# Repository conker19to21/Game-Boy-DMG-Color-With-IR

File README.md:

This Board is a modified version of <a href="https://github.com/MouseBiteLabs/Game-Boy-DMG-Color/tree/main/DMGC-CPU-01">Bucket Mouse's Original DMGC CPU board</a> which houses the majority of the electronics in the DMGC but adds the IR components and capability as well.

.png)
.png)

Shoutout to NatalieTheNerd for their amazing Reverse engineering work which was referrenced for this project and can be <a href="https://github.com/nataliethenerd/CGB_ReverseEngineer/tree/main">Found Here!</a>

Additional Major Shout Out goes to EdvinDraw!
A IR shield cutout was designed by EdvinDraw and can be <a href="https://www.thingiverse.com/thing:7093936">Found Here!</a> for use with NON clear DMG shells.

Additionally EdvinDraw had also made a Tutorial how to use and make the IR shield cutout which can be <a href="https://youtu.be/QVl8f0OApuU?si=GgzmjaVQX5JkgJGN">Found Here!</a>

Also note the IR was tested on some clear shells and worked fine without the cutout or IR shield but may still be needed for some.

Download and use the gerber.zip file at your preferred PCB manufacture and use these Board Characteristics for proper fitment.
## Board Characteristics
The gerber zipped folder contains all the gerber files for this board. 

-	Layers: 2
-	Thickness: 1.2 mm
-	Surface Finish: ENIG or HASL
-   **NOTE: When ordering PCBs, add this note to the order: "The file PTH-drl.gbr contains outlines for plated slots. Please add plated slots on the PCB according to this layer."**

*HASL will work, but will potentially be more difficult for soldering fine-pitch parts like the CPU and FFC connector.*

I do not take any credit for Bucket Mouse's Board Design only the modifications done and implementation for the IR components which were added to it.

Be sure to check out Bucket Mouse's Original Github Post on the DMGC project which can be <a href="https://github.com/MouseBiteLabs/Game-Boy-DMG-Color/tree/main">Found Here!</a> and has a Huge breakdown of common issues and solutions to most issues which may occur during the building process.

Version 2.0 of Bucket Mouse's original design introduced a test pad labelled "RST" that connects directly to the /RESET pin. If this pin is pulled to GND, when it's released then the system will reset back to the boot screen. If you wire this pad to a button that connects the pad to GND when pressed, you basically have added a reset button to your DMGC. 

There are also pads near the FFC connector that are added labelled "PUSH" and "ROCK DOWN". These connect to the rocker switch on the DMGC-IPS-01 board (version 2.0 and later). The PUSH pad becomes connected to GND when the rocker switch is pushed in and floats when not pressed (as long as you remove R10 on the DMGC-IPS-01 board). The ROCK_DOWN pad connects to GND when the rocker switch is rocked down, and floats when not pressed (as long as you remove C5 on the DMGC-IPS-01 board).

In a normal configuration, pushing in on the rocker switch will control the button LEDs, and rocking down will swap the Q5 color settings, but if you don't want to use one of these features, then adding a wire from the PUSH or ROCK DOWN pad to RST pad will turn the rocker switch into a reset button for the system for that specific action and replace its normal function.

**CAUTION: Remember to remove R10 or C5 on the IPS board if you plan to use this feature!!!**

## Bill of Materials

Here, I have provided links to components I used personally (or suitable replacements). This BOM is also included in Excel format in the root folder.

| Reference Designators                       | Qty | Value/Part Number | Package     | Description        | Comment                                                                 | Source                                                                                                                                                                                                                                                                                                                           |
| ------------------------------------------- | --- | ----------------- | ----------- | ------------------ | ----------------------------------------------------------------------- | -------------------------------------------------------------------------------------------------------------------------------------------------------------------------------------------------------------------------------------------------------------------------------------------------------------------------------- |
| +,-                                         | 2   |                   |             | Battery terminals  | Can be salvaged from DMG instead                                        | [https://retrogamerepairshop.com/collections/dmg-power/products/game-boy-dmg-original-high-quality-replacement-battery-contact-terminals?variant=37893135794348](https://retrogamerepairshop.com/collections/dmg-power/products/game-boy-dmg-original-high-quality-replacement-battery-contact-terminals?variant=37893135794348) |
| C1                                          | 1   | 18pF              | 0603        | Capacitor (MLCC)   | Should be X5R (or better); at least 1% tolerance; at least 16V          | [https://www.mouser.com/ProductDetail/YAGEO/CC0603FRNPO9BN180?qs=vTakOoo5QyL0KzYUzHPSUw%3D%3D](https://www.mouser.com/ProductDetail/YAGEO/CC0603FRNPO9BN180?qs=vTakOoo5QyL0KzYUzHPSUw%3D%3D)                                                                                                                                     |
| C2                                          | 1   | 27pF              | 0603        | Capacitor (MLCC)   | Should be X5R (or better); at least 1% tolerance; at least 16V          | [https://www.mouser.com/ProductDetail/603-C0603FRNPO9BN270](https://www.mouser.com/ProductDetail/603-C0603FRNPO9BN270)                                                                                                                                                                                                           |
| C4                                          | 1   | 22pF              | 0603        | Capacitor (MLCC)   |                                                                         | [https://www.mouser.com/ProductDetail/YAGEO/CC0603JRNPO9BN220?qs=vTakOoo5QyIVMYOUTI%2F4zA%3D%3D](https://www.mouser.com/ProductDetail/YAGEO/CC0603JRNPO9BN220?qs=vTakOoo5QyIVMYOUTI%2F4zA%3D%3D)                                                                                                                                 |
| C5, C6, C7                                  | 3   | 100pF             | 0603        | Capacitor (MLCC)   |                                                                         | [https://www.mouser.com/ProductDetail/YAGEO/CC0603JPNPO9BN101?qs=7s%252B3O6pAiyAo%2FUxNqKltRA%3D%3D](https://www.mouser.com/ProductDetail/YAGEO/CC0603JPNPO9BN101?qs=7s%252B3O6pAiyAo%2FUxNqKltRA%3D%3D)                                                                                                                         |
| C9, C10, C29, C33, C41, C45                 | 6   | 0.01uF            | 0603        | Capacitor (MLCC)   | Should be X5R (or better), at least 16V                                 | [https://www.mouser.com/ProductDetail/KEMET/C0603C103J5RACTU?qs=BimOss5pjlFJEfKhlb7g1g%3D%3D](https://www.mouser.com/ProductDetail/KEMET/C0603C103J5RACTU?qs=BimOss5pjlFJEfKhlb7g1g%3D%3D)                                                                                                                                       |
| C16, C17, C18, C19, C39, C40, C48, C49, C51 | 9   | 1uF               | 0603        | Capacitor (MLCC)   | Should be X5R (or better), at least 16V                                 | [https://www.mouser.com/ProductDetail/KEMET/C0603C105K4RACTU?qs=STjISULpmtZNMAZGR4X39Q%3D%3D](https://www.mouser.com/ProductDetail/KEMET/C0603C105K4RACTU?qs=STjISULpmtZNMAZGR4X39Q%3D%3D)                                                                                                                                       |
| C24, C28, C43, C52, C53                     | 5   | 0.1uF             | 0603        | Capacitor (MLCC)   | Should be X5R (or better), at least 16V                                 | [https://www.mouser.com/ProductDetail/?qs=l5k%252BbMnNDknCtKnMv1oEgA%3D%3D](https://www.mouser.com/ProductDetail/?qs=l5k%252BbMnNDknCtKnMv1oEgA%3D%3D)                                                                                                                                                                           |
| C47                                         | 1   | 150pF             | 0603        | Capacitor (MLCC)   |                                                                         | [https://www.mouser.com/ProductDetail/KEMET/C0603C151J5GACTU?qs=V6nSPVTm7vxbAvL0weNH%252BQ%3D%3D](https://www.mouser.com/ProductDetail/KEMET/C0603C151J5GACTU?qs=V6nSPVTm7vxbAvL0weNH%252BQ%3D%3D)                                                                                                                               |
| D1                                          | 1   | PMEG2010AEH       | SOD-123     | Schottky diode     | Most schottky diodes should be suitable (at least 1A, 16V)              | [https://www.mouser.com/ProductDetail/?qs=LOCUfHb8d9u7lcjEnyhX1g%3D%3D](https://www.mouser.com/ProductDetail/?qs=LOCUfHb8d9u7lcjEnyhX1g%3D%3D)                                                                                                                                                                                   |
| DC                                          | 1   |                   |             | DC jack            |                                                                         | Salvaged (DMG)                                                                                                                                                                                                                                                                                                                   |
| EM6-EM8                                     | 3   | FBMH2012HM221-T   | 0805        | Filter             |                                                                         | https://mou.sr/3YT6y8F                                                                                                                     |
| EM9                                         | 1   | BLM18BD102SN1D    | 0603        | Filter             |                                                                         | [https://www.mouser.com/ProductDetail/Murata-Electronics/BLM18BD102SN1D?qs=h3IWXJJGQQWi4eZyJq6ScQ%3D%3D](https://www.mouser.com/ProductDetail/Murata-Electronics/BLM18BD102SN1D?qs=h3IWXJJGQQWi4eZyJq6ScQ%3D%3D)                                                                                                                 |
| EM10                                        | 1   | 744235601         |             | Common mode filter | Can be salvaged from GBC instead                                        | [https://www.mouser.com/ProductDetail/Wurth-Elektronik/744235601?qs=BXmE%252BJ0Y7xYO4MPd53j2NQ%3D%3D](https://www.mouser.com/ProductDetail/Wurth-Elektronik/744235601?qs=BXmE%252BJ0Y7xYO4MPd53j2NQ%3D%3D)                                                                                                                       |
| F1                                          | 1   | 2.5A              | 1206        | Fuse               |                                                                         | [https://www.mouser.com/ProductDetail/Panasonic/ERB-RG2R50V?qs=Z3CaLxJiOJK8SjHyp%252BdV%2FQ%3D%3D](https://www.mouser.com/ProductDetail/Panasonic/ERB-RG2R50V?qs=Z3CaLxJiOJK8SjHyp%252BdV%2FQ%3D%3D)                                                                                                                             |
| F2                                          | 1   | 1A                | 1206        | Fuse               |                                                                         | [https://www.mouser.com/ProductDetail/Littelfuse/0466001.NR?qs=ar9f0rk5DXDy6tpNfF8WnQ%3D%3D](https://www.mouser.com/ProductDetail/Littelfuse/0466001.NR?qs=ar9f0rk5DXDy6tpNfF8WnQ%3D%3D)                                                                                                                                         |
| FB1                                         | 1   | BLA31AG601SN4D    | 1206        | Ferrite Bead       |                                                                         | [https://www.mouser.com/ProductDetail/Murata-Electronics/BLA31AG601SN4D?qs=2ahBf5rJw09FDcUVkQibEg%3D%3D](https://www.mouser.com/ProductDetail/Murata-Electronics/BLA31AG601SN4D?qs=2ahBf5rJw09FDcUVkQibEg%3D%3D)                                                                                                                 |
| P1                                          | 1   |                   |             | Cart connector     | Can be salvaged from DMG instead                                        | [https://www.aliexpress.com/item/3256802533298738.html?spm=a2g0o.order_list.0.0.5ee21802yek6HF](https://www.aliexpress.com/item/3256802533298738.html?spm=a2g0o.order_list.0.0.5ee21802yek6HF)                                                                                                                                   |
| P2                                          | 1   |                   |             | Link port          |                                                                         | Salvaged (DMG)                                                                                                                                                                                                                                                                                                                   |
| P3                                          | 1   | 62684-502100AHLF  |             | FFC connector      |                                                                         | [https://www.mouser.com/ProductDetail/?qs=HL%252BYNjdyZ0vzwc9E0QYY2g%3D%3D](https://www.mouser.com/ProductDetail/?qs=HL%252BYNjdyZ0vzwc9E0QYY2g%3D%3D)                                                                                                                                                                           |
| PTC1                                        | 1   | 1.1A Hold         | 1206        | Resettable Fuse    |                                                                         | [https://www.mouser.com/ProductDetail/Littelfuse/1206L110THYR?qs=CPcc0c%2Fon9HuH5Zb2mgbPg%3D%3D](https://www.mouser.com/ProductDetail/Littelfuse/1206L110THYR?qs=CPcc0c%2Fon9HuH5Zb2mgbPg%3D%3D)                                                                                                                                 |
| Q1                                          | 1   | SI1443EDH         | SOT363      | P-channel MOSFET   |                                                                         | [https://www.mouser.com/ProductDetail/Vishay-Semiconductors/SI1443EDH-T1-GE3?qs=vlV4ps1%252BrQifVq6ycRxedw%3D%3D](https://www.mouser.com/ProductDetail/Vishay-Semiconductors/SI1443EDH-T1-GE3?qs=vlV4ps1%252BrQifVq6ycRxedw%3D%3D)                                                                                               |
| R1                                          | 1   | 1k                | 0603        | Resistor           |                                                                         | [https://www.mouser.com/ProductDetail/YAGEO/RC0603FR-071KL?qs=VU8sRB4EgwApHsk4rF%2F3zg%3D%3D](https://www.mouser.com/ProductDetail/YAGEO/RC0603FR-071KL?qs=VU8sRB4EgwApHsk4rF%2F3zg%3D%3D)                                                                                                                                       |
| R3, R31, R33                                | 3   | 18k               | 0603        | Resistor           |                                                                         | [https://www.mouser.com/ProductDetail/YAGEO/RC0603FR-1018KL?qs=qpJ%252B%252B%252Bdg6p1T2VMMxU7GeA%3D%3D](https://www.mouser.com/ProductDetail/YAGEO/RC0603FR-1018KL?qs=qpJ%252B%252B%252Bdg6p1T2VMMxU7GeA%3D%3D)                                                                                                                 |
| R25                                         | 1   | 1.5M              | 0603        | Resistor           | Recommended at least 1% tolerance                                       | [https://www.mouser.com/ProductDetail/YAGEO/RC0603FR-071M5L?qs=VU8sRB4EgwAP38Z8qzPx9Q%3D%3D](https://www.mouser.com/ProductDetail/YAGEO/RC0603FR-071M5L?qs=VU8sRB4EgwAP38Z8qzPx9Q%3D%3D)                                                                                                                                         |
| R26                                         | 1   | 5.6k              | 0603        | Resistor           |                                                                         | [https://www.mouser.com/ProductDetail/YAGEO/RC0603FR-075K6L?qs=2cAdsCoAWRHvOVv%2Fp%252BkS0g%3D%3D](https://www.mouser.com/ProductDetail/YAGEO/RC0603FR-075K6L?qs=2cAdsCoAWRHvOVv%2Fp%252BkS0g%3D%3D)                                                                                                                             |
| R27                                         | 1   | 100               | 0603        | Resistor           |                                                                         | [https://www.mouser.com/ProductDetail/YAGEO/RC0603FR-07100RL?qs=NEN%2FsE%2FLsvPIwIWKCOS4%2FA%3D%3D](https://www.mouser.com/ProductDetail/YAGEO/RC0603FR-07100RL?qs=NEN%2FsE%2FLsvPIwIWKCOS4%2FA%3D%3D)                                                                                                                           |
| R36                                         | 1   | 100k              | 0603        | Resistor           |                                                                         | [https://www.mouser.com/ProductDetail/YAGEO/RC0603FR-07100KL?qs=e1ok2LiJcmaihem8Va5%2Fsw%3D%3D](https://www.mouser.com/ProductDetail/YAGEO/RC0603FR-07100KL?qs=e1ok2LiJcmaihem8Va5%2Fsw%3D%3D)                                                                                                                                   |
| R30, R32                                    | 2   | 47k               | 0603        | Resistor           |                                                                         | [https://www.mouser.com/ProductDetail/YAGEO/RC0603FR-1047KL?qs=EiqXWrxQq600ZhhpLJs%252BtA%3D%3D](https://www.mouser.com/ProductDetail/YAGEO/RC0603FR-1047KL?qs=EiqXWrxQq600ZhhpLJs%252BtA%3D%3D)                                                                                                                                 |
| RA1A, RA1B                                  | 2   | 510               | 0603        | Resistor           |                                                                         | [https://www.mouser.com/ProductDetail/YAGEO/RC0603FR-07510RL?qs=gt6vzsuosg04lV7mPQHzdw%3D%3D](https://www.mouser.com/ProductDetail/YAGEO/RC0603FR-07510RL?qs=gt6vzsuosg04lV7mPQHzdw%3D%3D)                                                                                                                                       |
| RA3A-RA3D                                   | 4   | 270               | 0603        | Resistor           |                                                                         | [https://www.mouser.com/ProductDetail/YAGEO/RC0603FR-07270RL?qs=diQw95jMAePl%252BPNr4oNP6Q%3D%3D](https://www.mouser.com/ProductDetail/YAGEO/RC0603FR-07270RL?qs=diQw95jMAePl%252BPNr4oNP6Q%3D%3D)                                                                                                                               |
| SW1                                         | 1   |                   |             | Power switch       |                                                                         | Salvaged (DMG)                                                                                                                                                                                                                                                                                                                   |
| U1                                          | 1   | GBC CPU           | QFP-128     | CPU                |                                                                         | Salvaged (GBC)                                                                                                                                                                                                                                                                                                                   |
| U2                                          | 1   | LH52256CVTXIZ     | TSOP-28     | RAM                | Replacement: https://mou.sr/3f8G0Mi                                     | Salvaged (GBC)                                                                                                                                                                                                                                                                                                                   |
| U3                                          | 1   | LM4853            | VSSOP-10    | Audio amplifier    |                                                                         | [https://www.mouser.com/ProductDetail/Texas-Instruments/LM4853MM-NOPB?qs=QbsRYf82W3F2psFI2da2Dw%3D%3D](https://www.mouser.com/ProductDetail/Texas-Instruments/LM4853MM-NOPB?qs=QbsRYf82W3F2psFI2da2Dw%3D%3D)                                                                                                                     |
| U4                                          | 1   | NCP161ASN330T1G   | SOT23-5     | LDO                | Can also use TLV70233QDBVRQ1, probably                                  | [https://www.mouser.com/ProductDetail/863-NCP161ASN330T1G](https://www.mouser.com/ProductDetail/863-NCP161ASN330T1G)                                                                                                                                                                                                             |
| U6                                          | 1   | TPS3840DL35       | SOT23-5     | Supervisory IC     | Could feasibly use TPS3840DL37 or 40 if 35 is out of stock              | [https://www.mouser.com/ProductDetail/Texas-Instruments/TPS3840DL35DBVR?qs=7MVldsJ5UawbjRj7dP73rA%3D%3D](https://www.mouser.com/ProductDetail/Texas-Instruments/TPS3840DL35DBVR?qs=7MVldsJ5UawbjRj7dP73rA%3D%3D)                                                                                                                 |
| VR1                                         | 1   | 10k               |             | Volume wheel       | Can be salvaged from DMG instead                                        | [https://aliexpi.com/qg1M](https://aliexpi.com/qg1M)                                                                                                                                                                                                                                                                             |
| X1                                          | 1   | 8.388608MHz       | 7.5X5-4-PAD | Crystal oscillator | Potential replacement (not very space-friendly): https://mou.sr/3D5AUbH | Salvaged (GBC)                                                                                                                                                                                                                                                                                                                   |
| C13                                          | 1   | 470nF       | 0603 Capacitor | Capacitor (MLCC) |  | [https://mou.sr/4cTTRzx](https://mou.sr/4cTTRzx)
| C20                                          | 1   | 15nF       | 0603 Capacitor | Capacitor (MLCC) |  | [https://mou.sr/4jKsSIQ](https://mou.sr/4jKsSIQ)
| C21                                          | 1   | 1uF       | 0603 Capacitor | Capacitor (MLCC) |  | [https://mou.sr/47lY3oP](https://mou.sr/47lY3oP)
| C22                                          | 1   | 33pF       | 0603 Capacitor | Capacitor (MLCC) |  | [https://mou.sr/4cMeVrs](https://mou.sr/4cMeVrs)
| D2                                          | 1   | GL381       |  | 3mm Infrared LED |  | Salvaged (GBC)
| Q2, Q3                                          | 2  | 2SC4081       | SOT-323 / SC-70 |  |  | [https://mou.sr/3XxVZGQ](https://mou.sr/3XxVZGQ)             
| Q4                                          | 1   | PT380F       |  | 3mm Phototransistor |  | Salvaged (GBC)
| R12                                          | 1   | 4.7k ohm       | 0603 Capacitor | Resistor |  |  [https://mou.sr/41PpIxl](https://mou.sr/41PpIxl)
| R13, R16                                         | 2   | 33k ohm       | 0603 Capacitor | Resistor |  |  [https://mou.sr/3DVwgBw](https://mou.sr/3DVwgBw)
| R15                                          | 1   | 1M ohm       | 0603 Capacitor | Resistor |  |  [https://mou.sr/4iLYdL4](https://mou.sr/4iLYdL4)
| R17                                          | 1   | 200k ohm       | 0603 Capacitor | Resistor |  |  [https://mou.sr/4cdZFn6](https://mou.sr/4cdZFn6)
| R18                                          | 1   | 150 ohm       | 0603 Capacitor | Resistor |  |  [https://mou.sr/4l9UBnU](https://mou.sr/4l9UBnU)
| R19                                          | 1   | 1k ohm       | 0603 Capacitor | Resistor |  |  [https://mou.sr/3U0EvS4](https://mou.sr/3U0EvS4)
| R20                                          | 1   | 2k ohm       | 0603 Capacitor | Resistor |  |  [https://mou.sr/4j6GOfR](https://mou.sr/4j6GOfR)
| GBC IR Shield                                          | 1   |       | | IR Shield |  |  Salvaged (GBC)

## License
<br />This work is licensed under a <a rel="license" href="http://creativecommons.org/licenses/by-sa/4.0/">Creative Commons Attribution-ShareAlike 4.0 International License</a>. You are able to copy and redistribute the material in any medium or format, as well as remix, transform, or build upon the material for any purpose (even commercial) - but you **must** give appropriate credit, provide a link to the license, and indicate if any changes were made.

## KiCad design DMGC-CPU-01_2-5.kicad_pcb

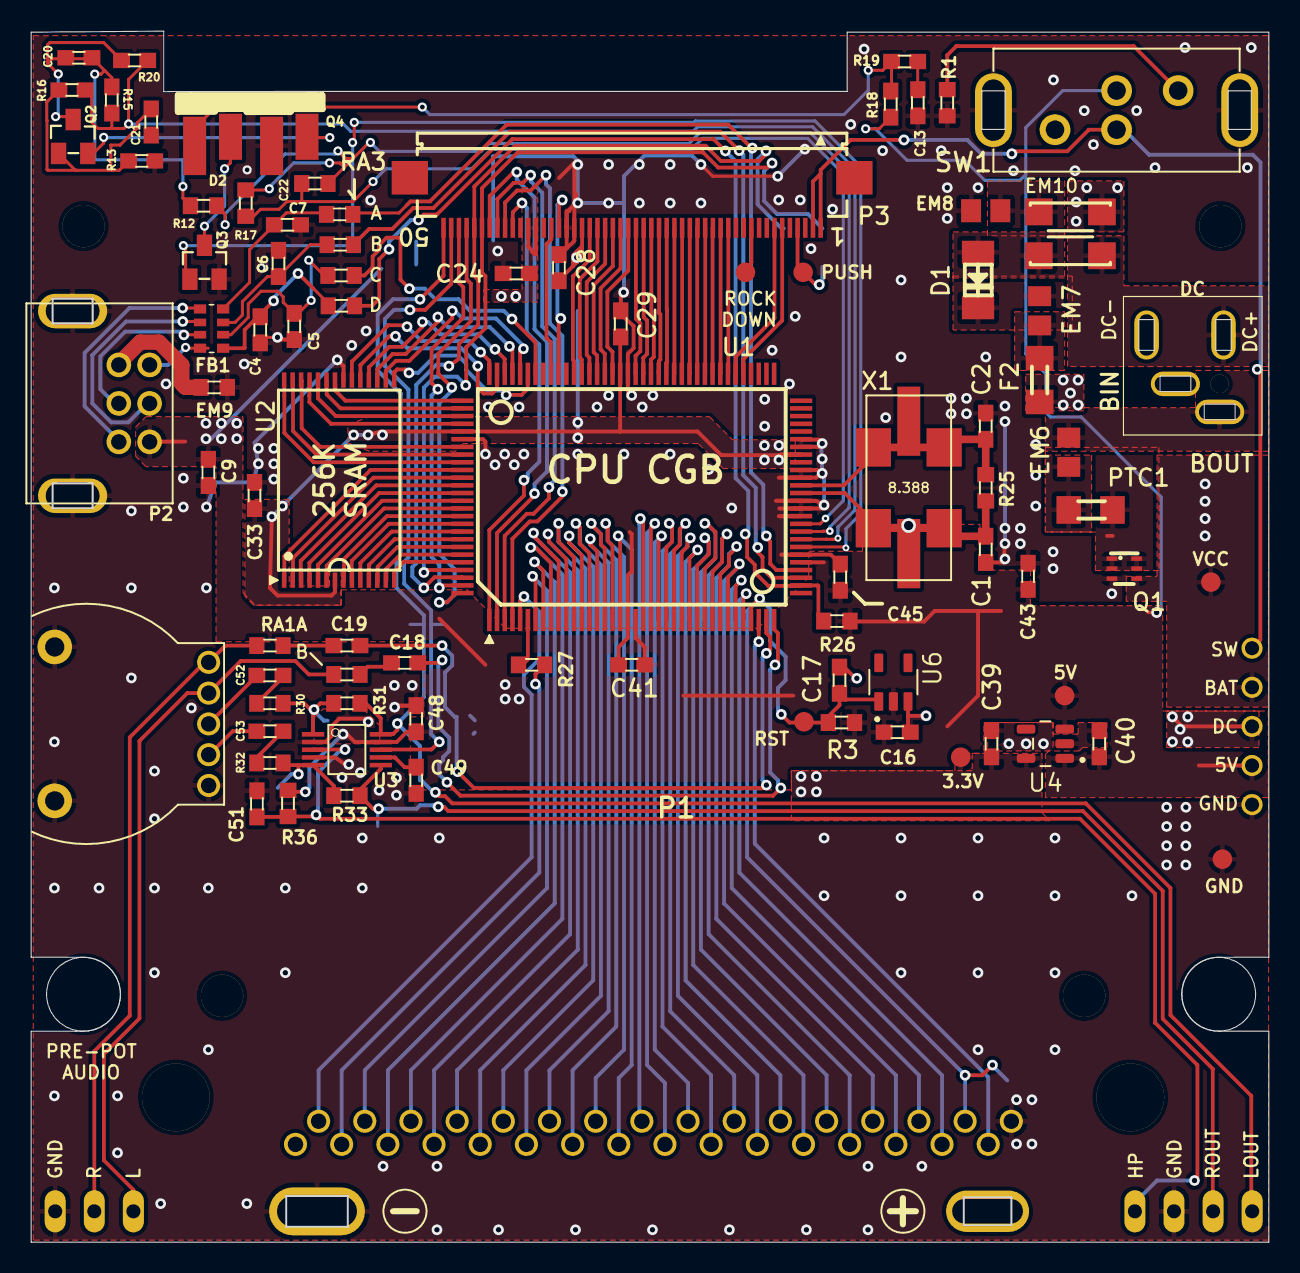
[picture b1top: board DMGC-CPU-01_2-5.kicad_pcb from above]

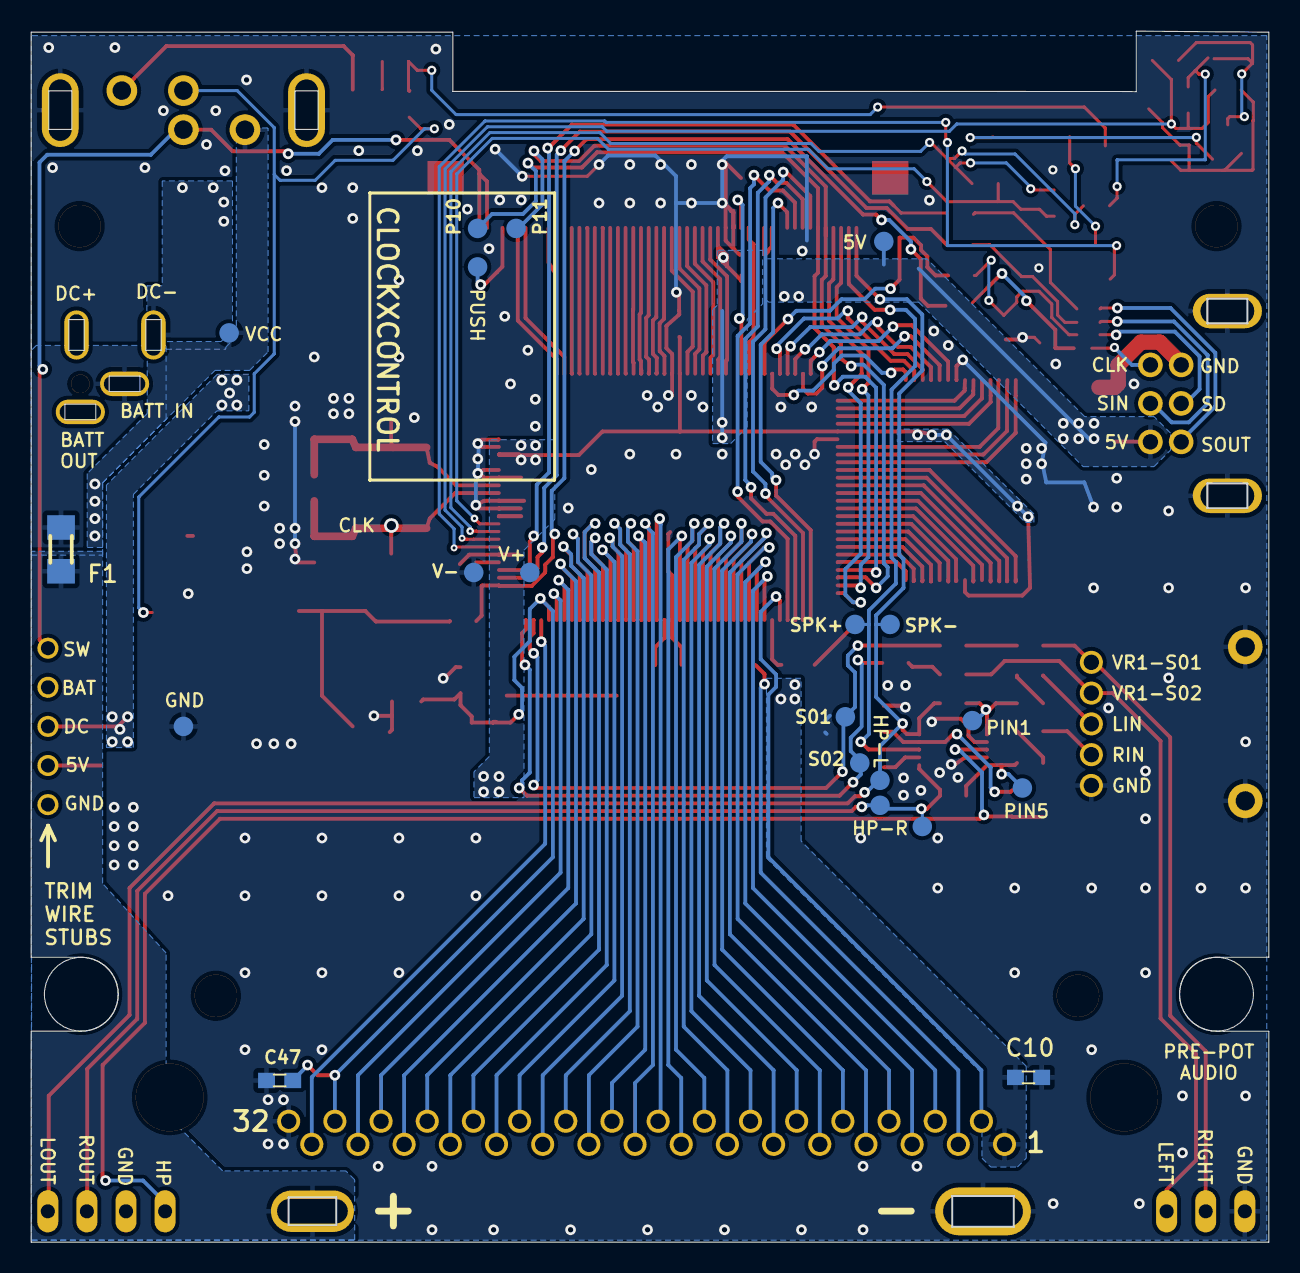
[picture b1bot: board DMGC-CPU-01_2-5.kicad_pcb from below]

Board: 2 copper layers, 80.4 x 78.7 mm, 125 parts (20 on the bottom side), 143 nets.

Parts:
3.3V, 5V: PTR1B1,27; B1,27_385
+0: DMG_BAT_POS
-0: DMG_BAT_NEG
@HOLE0, @HOLE1, @HOLE2, @HOLE3, @HOLE4, @HOLE5, @HOLE6, @HOLE7: (no value)
AUDIO0: JP4
C1: 18pF; C0603
C2: 27pF; C0603
C4: 22pF; C0603
C5, C6, C7: 100pF; C0603
C9, C10, C29, C33, C41, C45: 0.01uF; C0603
C13: 0.47uF; C0603
C16, C17, C18, C19, C21, C39, C40, C48, C49, C51: 1uF; C0603
C20: 0.015uF; C0603
C22: 33pF; R0603
C24, C28, C43: 0.1uF; C0603
C47: 150pF; C0603
C52, C53: 100nF; C0603
D1: CGRM4001-G; SOD-123_MINI-SMA_210
D2, D2#2: GL381
DC: DMG_DCJACK
EM6, EM7, EM8: BLM21P221SG; R0805
EM9: BLM21P221SG; R0603
EM10: ACM4532
F1: 2.5A; R1206
F2: 1A; R1206
FB1: 4W601; EXB38V_342
GND: PTR1B1,27; B1,27_385
GND_BACK0: PTR1B1,27; B1,27_385
JP1: JP5
JP2: JP2
LOUT0: PTR1B1,27; B1,27_385
P1: DMG_CART
P2: LINKPORTDMG-LINK-SHORT; DMG_EXT
P3: GBC_LCDH; 62684-502100AHLF
P10, P11: PTR1B1,27; B1,27_385
PIN1, PIN5: PTR1B1,27; B1,27_385
PSH_IN0: PTR1B1,27; B1,27_385
PTC1: 1.1A; R1206
PUSH: PTR1B1,27; B1,27_385
Q1: SI1401EDH; SOT363_INFINEON_396
Q2, Q2#2, Q2#3, Q3, Q3#2, Q3#3: 2SC4081
Q4, Q4#2: PT380F
R1: 1k; R0603
R3, R31, R33: 18k; R0603
R12: 4.7k; R0603
R13, R16: 33k; C0603
R15: 1M; C0603
R17: 200k; R0603
R18: 150; C0603
R19: 1k; C0603
R20: 2k; C0603
R25: 1.5M; R0603
R26: 5.6k; R0603
R27: 100; R0603
R30, R32: 47k; R0603
R36: 100k; R0603
RA1A, RA1B0: 510; R0603
RA3A0, RA3B0, RA3C0, RA3D0: 270; R0603
ROCKDOWN0: PTR1B1,27; B1,27_385
ROUT0, ROUT1: PTR1B1,27; B1,27_385
RST: PTR1B1,27; B1,27_385
S01, S02: PTR1B1,27; B1,27_385
SPK+: PTR1B1,27; B1,27_385
SPK-: PTR1B1,27; B1,27_385
SW1: DMG_SW
U1: GBC_CPU; QFP-128
U2: LH52256CVTCZ; TSOP1-28
U3: LM4853; VSSOP10
U4: TLV70233QDBVRQ1; SOT95P280X145-5N
U6: TPS3840; SOT-23-5
UNK3.3V_BACK0, UNK5V_BACK0: PTR1B1,27; B1,27_385
V-: PTR1B1,27; B1,27_385
VCC: PTR1B1,27; B1,27_385
VCC_BACK0: PTR1B1,27; B1,27_385
VR1: DMG_VOL
X1: 8.388608MHZ12SMX-B-4-PAD; 7.5X5-4-PAD

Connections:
+3V3: 3.3V.TP, C28.2, C29.1, C33.1, C39.1, P3.32 (1), U1.57 (~\NMI), U1.85 (VDD3@85), U1.107 (VDD3@107), U2.7 (VCC), U4.5 (OUT), UNK3.3V_BACK0.TP
+5V: 5V.TP, C9.1, C10.1, C16.1, C24.1, C40.1, C41.1, C43.1, C45.1, C48.1, JP1.2, P1.1 (VCC), P2.+5V, P3.38 (1), P3.39 (1), R3.1, R18.1, R26.2, R36.2, SW1.P$3 (3), U1.20 (VDD5@20), U1.43 (VDD5@43), U3.9 (VDD), U4.1 (IN), U4.3 (EN), U6.2 (VDD), UNK5V_BACK0.TP
/A0: P1.6 (A0), U1.9 (A0)
/A1: P1.7 (A1), U1.10 (A1)
/A2: P1.8 (A2), U1.11 (A2)
/A3: P1.9 (A3), U1.12 (A3)
/A4: P1.10 (A4), U1.13 (A4)
/A5: P1.11 (A5), U1.14 (A5)
/A6: P1.12 (A6), U1.15 (A6)
/A7: P1.13 (A7), U1.16 (A7)
/A8: P1.14 (A8), U1.17 (A8)
/A9: P1.15 (A9), Q2#2.2 (S), Q4#2.5, U1.18 (A9)
/A10: P1.16 (A10), U1.21 (A10)
/A11: P1.17 (A11), U1.22 (A11)
/A12: P1.18 (A12), U1.23 (A12)
/A13: P1.19 (A13), U1.24 (A13)
/A14: P1.20 (A14), U1.25 (A14)
/A15: P1.21 (A15), U1.26 (A15)
/BATT: +0.P$1, F1.1
/CK1: C1.1, D2.5, R18.2, R19.1, R25.1, U1.52 (CK1), X1.1, X1.4, X1.5
/CK2: C2.1, R25.2, U1.53 (CK2), X1.2, X1.3, X1.6
/CLS: P3.7 (1), U1.70 (CLS)
/CS: P1.5 (~CS), U1.8 (~CS)
/D0: P1.22 (D0), U1.27 (D0)
/D1: P1.23 (D1), U1.28 (D1)
/D2: P1.24 (D2), U1.29 (D2)
/D3: D2#2.5, P1.25 (D3), Q3#2.3 (D), U1.30 (D3)
/D4: P1.26 (D4), U1.31 (D4)
/D5: P1.27 (D5), U1.32 (D5)
/D6: P1.28 (D6), U1.33 (D6)
/D7: P1.29 (D7), U1.34 (D7)
/DCK: P3.36 (1), U1.94 (DCK)
/DC_JACK: F2.1, JP1.3
/ELP2: FB1.1, P2.OUT
/ELP3: FB1.2 (1), P2.IN
/ELP4: FB1.3 (1), P2.SD
/ELP5: FB1.4 (1), P2.CLK
/HP_SWITCH: AUDIO0.1, C51.1, R36.1, U3.3 (HP_IN)
/LDB0: P3.26 (1), U1.86 (LDB0)
/LDB1: P3.27 (1), U1.87 (LDB1)
/LDB2: P3.28 (1), U1.88 (LDB2)
/LDB3: P3.29 (1), U1.89 (LDB3)
/LDB4: P3.30 (1), U1.90 (LDB4)
/LDB5: P3.31 (1), U1.91 (LDB5)
/LDG0: P3.20 (1), U1.78 (LDG0)
/LDG1: P3.21 (1), U1.79 (LDG1)
/LDG2: P3.22 (1), U1.80 (LDG2)
/LDG3: P3.23 (1), U1.81 (LDG3)
/LDG4: P3.24 (1), U1.82 (LDG4)
/LDG5: P3.25 (1), U1.83 (LDG5)
/LDR0: P3.14 (1), U1.72 (LDR0)
/LDR1: P3.15 (1), U1.73 (LDR1)
/LDR2: P3.16 (1), U1.74 (LDR2)
/LDR3: P3.17 (1), U1.75 (LDR3)
/LDR4: P3.18 (1), U1.76 (LDR4)
/LDR5: P3.19 (1), U1.77 (LDR5)
/LIN_AMP: PIN1.TP, R30.1, R31.2, U3.1 (LIN)
/LP: P3.35 (1), U1.93 (LP)
/MA0: U1.99 (MA0), U2.17 (A0)
/MA1: U1.98 (MA1), U2.16 (A1)
/MA2: U1.97 (MA2), U2.15 (A2)
/MA3: U1.124 (MA3), U2.14 (A3)
/MA4: U1.123 (MA4), U2.13 (A4)
/MA5: U1.122 (MA5), U2.12 (A5)
/MA6: U1.121 (MA6), U2.11 (A6)
/MA7: U1.120 (MA7), U2.10 (A7)
/MA8: U1.115 (MA8), U2.4 (A8)
/MA9: U1.114 (MA9), U2.3 (A9)
/MA10: U1.111 (MA10), U2.28 (A10)
/MA11: U1.113 (MA11), U2.2 (A11)
/MA12: U1.119 (MA12), U2.9 (A12)
/MD0: U1.100 (MD0), U2.18 (DQ0)
/MD1: U1.101 (MD1), U2.19 (DQ1)
/MD2: U1.102 (MD2), U2.20 (DQ2)
/MD3: U1.103 (MD3), U2.22 (DQ3)
/MD4: U1.104 (MD4), U2.23 (DQ4)
/MD5: U1.105 (MD5), U2.24 (DQ5)
/MD6: U1.106 (MD6), U2.25 (DQ6)
/MD7: U1.109 (MD7), U2.26 (DQ7)
/P00: P3.41 (1), U1.1 (P00)
/P01: P3.42 (1), U1.4 (P01)
/P02: P3.43 (1), U1.3 (P02)
/P03: P3.44 (1), U1.2 (P03)
/P10: P3.45 (1), P10.TP, U1.125 (P10)
/P11: P3.46 (1), P11.TP, U1.126 (P11)
/P12: P3.47 (1), U1.128 (P12)
/P13: P3.48 (1), U1.127 (P13)
/PUSH: P3.4 (1), PSH_IN0.TP, PUSH.TP
/R0: Q3.1 (G), U1.45 (R0)
/R1: R15.1, R16.1, R20.1, U1.46 (R1)
/R2: C22.1, R12.2, R17.2, U1.47 (R2)
/R3: C22.2, R17.1, U1.48 (R3)
/R4: RA3C0.2, U1.96 (R4)
/RA0: U1.116 (RA0), U2.5 (A13)
/RA1: U1.118 (RA1), U2.8 (A14)
/RA1-S01: C19.2, RA1A.2
/RA1-S02: C18.2, RA1B0.2
/RD: P1.4 (~RD), U1.7 (~RD)
/RES: C17.1, C47.1, P1.30 (~RST), R3.2, RST.TP, U1.35 (~RESET), U6.1 (~RESET)
/RIN_AMP: PIN5.TP, R32.1, R33.2, U3.5 (RIN)
/ROCK_DOWN: P3.10 (1), ROCKDOWN0.TP
/ROUT: AUDIO0.3, R33.1, ROUT0.TP, ROUT1.TP, U3.6 (ROUT)
/S01: C19.1, S01.TP, U1.37 (S01)
/S02: C18.1, S02.TP, U1.38 (S02)
/SCK: R26.1, RA3D0.2, U1.40 (SCK)
/SIN: RA3B0.2, U1.41 (SIN)
/SOUT: RA3A0.2, U1.42 (SOUT)
/SPK+: P3.49 (1), SPK+.TP, U3.8 (BTL+)
/SPK-: AUDIO0.4, LOUT0.TP, P3.50 (1), R31.1, SPK-.TP, U3.10 (LOUT/BTL-)
/SPL: P3.13 (1), U1.71 (SPL)
/SPS: P3.6 (1), U1.69 (SPS)
/VCC_SW: JP1.5, P3.1, P3.2 (1), SW1.P$1 (1)
/VIN: P1.31 (SND), U1.36 (VIN)
/VR1-S01: JP2.2, RA1A.1, VR1.P$5 (VR1-S01)
/VR1-S02: JP2.3, RA1B0.1, VR1.P$4 (VR1-S02)
/WR: P1.3 (~WR), R27.2
/~CS1: U1.110 (~\CS1), U2.27 (~CE)
/~MRD: U1.112 (~\MRD), U2.1 (~OE)
/~MWR: U1.117 (~\MWR), U2.6 (~WE)
GND: -0.P$1, AUDIO0.2, C1.2, C2.2, C4.2, C5.2, C6.2, C7.2, C9.2, C10.2, C13.1, C16.2, C17.2, C21.2, C24.2, C28.1, C29.2, C33.2, C39.2, C40.2, C41.2, C43.2, C45.2, C47.2, C48.2, C49.2, C51.2, EM8.2, EM9.2, GND.TP, GND_BACK0.TP, JP1.1, JP2.1, P1.32 (GND), P2.SHIELD, P2.SHIELD1, P3.33 (1), P3.34 (1), Q1.3 (G), Q3#3.2 (S), Q4.5, R1.2, R13.2, SW1.P$7, SW1.P$8, U1.19 (GND@19), U1.44 (GND@44), U1.49 (TEST0), U1.50 (TEST1), U1.51 (TEST2), U1.54 (PSMD0), U1.55 (PSMD1), U1.58 (~MCS0), U1.59 (~MCS1), U1.84 (GND@84), U1.108 (GND@108), U2.21 (GND), U3.2 (SHTDWN), U3.4 (GND), U4.2 (GND), U6.3 (GND), V-.TP, VR1.P$1 (GND), VR1.P$6, VR1.P$7
unnamed: C13.2, C20.2, C52.2, Q2#3.3 (D), R19.2, R20.2, R30.2
unnamed: C20.1, C53.2, R12.1, R15.2, R32.2
unnamed: D1.A, EM10.4
unnamed: D1.C, EM7.1
unnamed: DC.2 (DC), EM10.1
unnamed: DC.1 (GND), EM10.2
unnamed: DC.3 (SWA), EM6.1
unnamed: DC.4 (SWB), F1.2
unnamed: EM6.2, PTC1.2
unnamed: EM7.2, F2.2
unnamed: EM9.1, P2.GND
unnamed: EM8.1, EM10.3
unnamed: C7.1, FB1.8 (2), RA3A0.1
unnamed: C6.1, FB1.7 (2), RA3B0.1
unnamed: C5.1, FB1.6 (2), RA3C0.1
unnamed: C4.1, FB1.5 (2), RA3D0.1
unnamed: PTC1.1, Q1.1 (D1), Q1.2 (D2), Q1.5 (D5), Q1.6 (D6)
unnamed: R1.1, SW1.P$4 (4)
unnamed: R27.1, U1.6 (~WR)
unnamed: C49.1, U3.7 (BYPASS)
unnamed: C52.1, VR1.P$3 (LIN)
unnamed: C53.1, VR1.P$2 (RIN)
VCC: JP1.4, Q1.4 (S), SW1.P$2 (2), VCC.TP, VCC_BACK0.TP

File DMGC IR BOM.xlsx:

CPU-01 IR | C13 |  | 470nF | 0603 Capacitor | Capacitor (MLCC) |  | https://mou.sr/4cTTRzx
 | C20 |  | 15nF | 0603 Capacitor | Capacitor (MLCC) |  | https://mou.sr/4jKsSIQ
 | C21 |  | 1uF | 0603 | Capacitor (MLCC) |  | https://www.mouser.com/ProductDetail/KEMET/C0603C105K4RACTU?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
 | C22 |  | 33pF | 0603 Capacitor | Capacitor (MLCC) |  | https://mou.sr/4cMeVrs
 | D2 |  | GL381 | 3mm Infrared LED |  |  | Salvaged (GBC)
 | Q2 |  | 2SC4081 | SOT-323 / SC-70 |  |  | https://mou.sr/3XxVZGQ
 | Q3 |  | 2SC4081 | SOT-323 / SC-70 |  |  | https://mou.sr/3XxVZGQ
 | Q4 |  | PT380F | 3mm Phototransistor |  |  | Salvaged (GBC)
 | R12 |  | 4.7k ohm | 0603 Capacitor | Resistor |  | https://mou.sr/41PpIxl
 | R13 |  | 33k ohm | 0603 Capacitor | Resistor |  | https://mou.sr/3DVwgBw
 | R15 |  | 1M ohm | 0603 Capacitor | Resistor |  | https://mou.sr/4iLYdL4
 | R16 |  | 33k ohm | 0603 Capacitor | Resistor |  | https://mou.sr/3DVwgBw
 | R17 |  | 200k ohm | 0603 Capacitor | Resistor |  | https://mou.sr/4cdZFn6
 | R18 |  | 150 ohm | 0603 Capacitor | Resistor |  | https://mou.sr/4l9UBnU
 | R19 |  | 1k ohm | 0603 | Resistor |  | https://www.mouser.com/ProductDetail/YAGEO/RC0603FR-071KL?qs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
 | R20 |  | 2k ohm | 0603 Capacitor | Resistor |  | https://mou.sr/4j6GOfR
CPU-01 | -/+ | 2.0 |  |  | Battery terminals | Can be salvaged from DMG instead | https://retrogamerepairshop.com/collections/dmg-power/produc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
 | C1 | 1.0 | 18pF | 603.0 | Capacitor (MLCC) | Should be X5R (or better); at least 1% tolerance; at least 16V | https://www.mouser.com/ProductDetail/YAGEO/CC0603FRNPO9BN180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
 | C2 | 1.0 | 27pF | 603.0 | Capacitor (MLCC) | Should be X5R (or better); at least 1% tolerance; at least 16V | https://www.mouser.com/ProductDetail/603-C0603FRNPO9BN270
 | C4 | 1.0 | 22pF | 603.0 | Capacitor (MLCC) |  | https://www.mouser.com/ProductDetail/YAGEO/CC0603JRNPO9BN220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
 | C5, C6, C7 | 3.0 | 100pF | 603.0 | Capacitor (MLCC) |  | https://www.mouser.com/ProductDetail/YAGEO/CC0603JPNPO9BN101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
 | C9, C10, C29, C33, C41, C45 | 6.0 | 0.01uF | 603.0 | Capacitor (MLCC) | Should be X5R (or better), at least 16V | https://www.mouser.com/ProductDetail/KEMET/C0603C103J5RACTU?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
 | C16, C17, C18, C19, C39, C40, C48, C49, C51 | 9.0 | 1uF | 603.0 | Capacitor (MLCC) | Should be X5R (or better), at least 16V | https://www.mouser.com/ProductDetail/KEMET/C0603C105K4RACTU?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
 | C24, C28, C43, C52, C53 | 5.0 | 0.1uF | 603.0 | Capacitor (MLCC) | Should be X5R (or better), at least 16V | https://www.mouser.com/ProductDetail/?qs=l5k%252BbMnNDknCtKn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
 | C47 | 1.0 | 150pF | 603.0 | Capacitor (MLCC) |  | https://www.mouser.com/ProductDetail/KEMET/C0603C151J5GACTU?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
 | D1 | 1.0 | PMEG2010AEH | SOD-123 | Schottky diode | Most schottky diodes should be suitable (at least 1A, 16V) | https://www.mouser.com/ProductDetail/?qs=LOCUfHb8d9u7lcjEnyh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
 | DC | 1.0 |  |  | DC jack |  | Salvaged (DMG)
 | EM6-EM8 | 3.0 | FBMH2012HM221-T | 805.0 | Filter |  | https://mou.sr/3YT6y8F
 | EM9 | 1.0 | BLM18BD102SN1D | 603.0 | Filter |  | https://www.mouser.com/ProductDetail/Murata-Electronics/BLM1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
 | EM10 | 1.0 | 7.44235601E8 |  | Common mode filter | Can be salvaged from GBC instead | https://www.mouser.com/ProductDetail/Wurth-Elektronik/744235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
 | F1 | 1.0 | 2.5A | 1206.0 | Fuse |  | https://www.mouser.com/ProductDetail/Panasonic/ERB-RG2R50V?q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
 | F2 | 1.0 | 1A | 1206.0 | Fuse |  | https://www.mouser.com/ProductDetail/Littelfuse/0466001.NR?q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
 | FB1 | 1.0 | BLA31AG601SN4D | 1206.0 | Ferrite Bead |  | https://www.mouser.com/ProductDetail/Murata-Electronics/BLA3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
 | P1 | 1.0 |  |  | Cart connector | Can be salvaged from DMG instead | https://www.aliexpress.com/item/3256802533298738.html?spm=a2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
 | P2 | 1.0 |  |  | Link port |  | Salvaged (DMG)
 | P3 | 1.0 | 62684-502100AHLF |  | FFC connector |  | https://www.mouser.com/ProductDetail/?qs=HL%252BYNjdyZ0vzwc9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
 | PTC1 | 1.0 | 1.1A Hold | 1206.0 | Resettable Fuse |  | https://www.mouser.com/ProductDetail/Littelfuse/1206L110THYR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
 | Q1 | 1.0 | SI1443EDH | SOT363 | P-channel MOSFET |  | https://www.mouser.com/ProductDetail/Vishay-Semiconductors/S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
 | R1 | 1.0 | 1k | 603.0 | Resistor |  | https://www.mouser.com/ProductDetail/YAGEO/RC0603FR-071KL?qs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
 | R3, R31, R33 | 3.0 | 18k | 603.0 | Resistor |  | https://www.mouser.com/ProductDetail/YAGEO/RC0603FR-1018KL?q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
 | R25 | 1.0 | 1.5M | 603.0 | Resistor | Recommended at least 1% tolerance | https://www.mouser.com/ProductDetail/YAGEO/RC0603FR-071M5L?q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
 | R26 | 1.0 | 5.6k | 603.0 | Resistor |  | https://www.mouser.com/ProductDetail/YAGEO/RC0603FR-075K6L?q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
 | R27 | 1.0 | 100.0 | 603.0 | Resistor |  | https://www.mouser.com/ProductDetail/YAGEO/RC0603FR-07100RL?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
 | R36 | 1.0 | 100k | 603.0 | Resistor |  | https://www.mouser.com/ProductDetail/YAGEO/RC0603FR-07100KL?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
 | R30, R32 | 2.0 | 47k | 603.0 | Resistor |  | https://www.mouser.com/ProductDetail/YAGEO/RC0603FR-1047KL?q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
 | RA1A, RA1B | 2.0 | 510.0 | 603.0 | Resistor |  | https://www.mouser.com/ProductDetail/YAGEO/RC0603FR-07510RL?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
 | RA3A-RA3D | 4.0 | 270.0 | 603.0 | Resistor |  | https://www.mouser.com/ProductDetail/YAGEO/RC0603FR-07270RL?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
 | SW1 | 1.0 |  |  | Power switch |  | Salvaged (DMG)
 | U1 | 1.0 | GBC CPU | QFP-128 | CPU |  | Salvaged (GBC)
 | U2 | 1.0 | LH52256CVTXIZ | TSOP-28 | RAM | Replacement: https://mou.sr/3f8G0Mi | Salvaged (GBC)
 | U3 | 1.0 | LM4853 | VSSOP-10 | Audio amplifier |  | https://www.mouser.com/ProductDetail/Texas-Instruments/LM485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
 | U4 | 1.0 | NCP161ASN330T1G | SOT23-5 | LDO | Can also use TLV70233QDBVRQ1, probably | https://www.mouser.com/ProductDetail/863-NCP161ASN330T1G
 | U6 | 1.0 | TPS3840DL35 | SOT23-5 | Supervisory IC | Could feasibly use TPS3840DL37 or 40 if 35 is out of stock | https://www.mouser.com/ProductDetail/Texas-Instruments/TPS38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
 | VR1 | 1.0 | 10k |  | Volume wheel | Can be salvaged from DMG instead | https://aliexpi.com/qg1M
 | X1 | 1.0 | 8.388608MHz | 7.5X5-4-PAD | Crystal oscillator | Potential replacement (not very space-friendly): https://mou.sr/3D5AUbH | Salvaged (GBC)

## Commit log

2025-07-20 DMGC IR Readme.md

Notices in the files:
README.md:
License:
This work is licensed under a Creative Commons Attribution-ShareAlike 4.0 International License. You are able to copy and redistribute the material in any medium or format, as well as remix, transform, or build upon the material for any purpose (even commercial) - but you **must** give appropriate credit, provide a link to
